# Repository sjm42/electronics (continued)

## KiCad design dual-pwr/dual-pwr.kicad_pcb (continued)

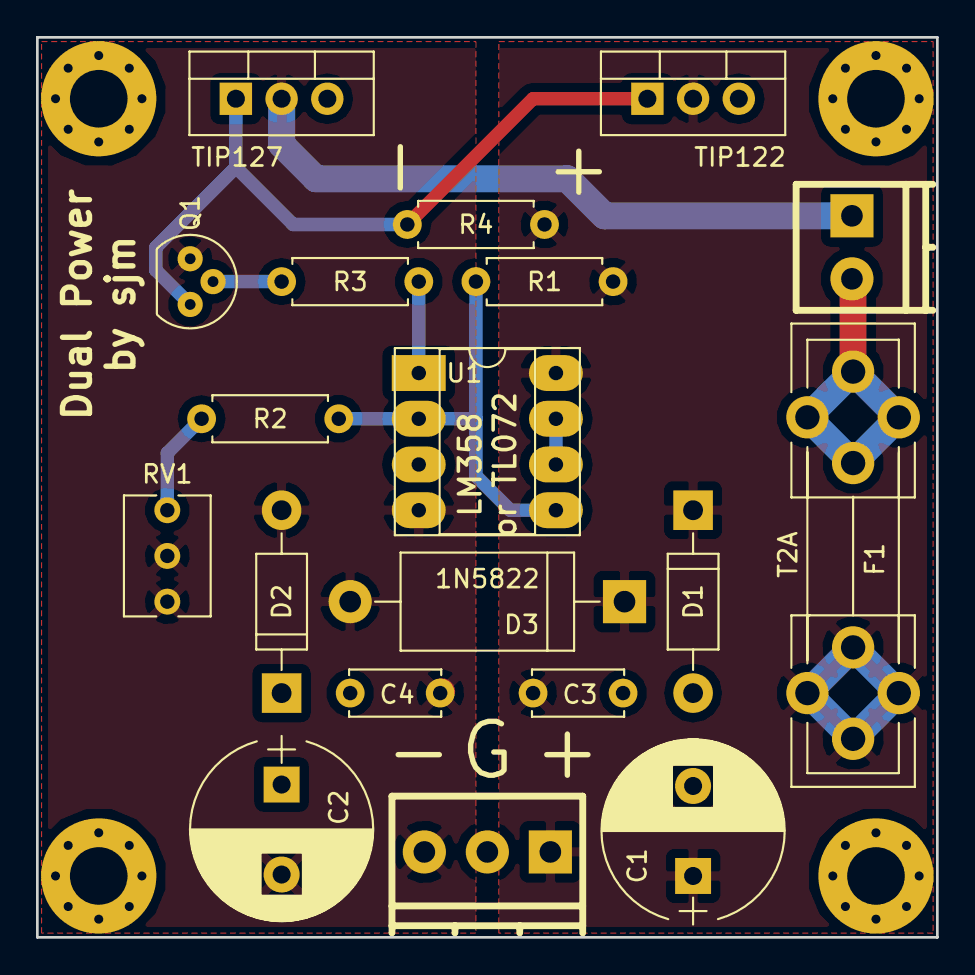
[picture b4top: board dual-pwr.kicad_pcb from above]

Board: 2 copper layers, 50.0 x 50.0 mm, 23 parts (0 on the bottom side), 10 nets.

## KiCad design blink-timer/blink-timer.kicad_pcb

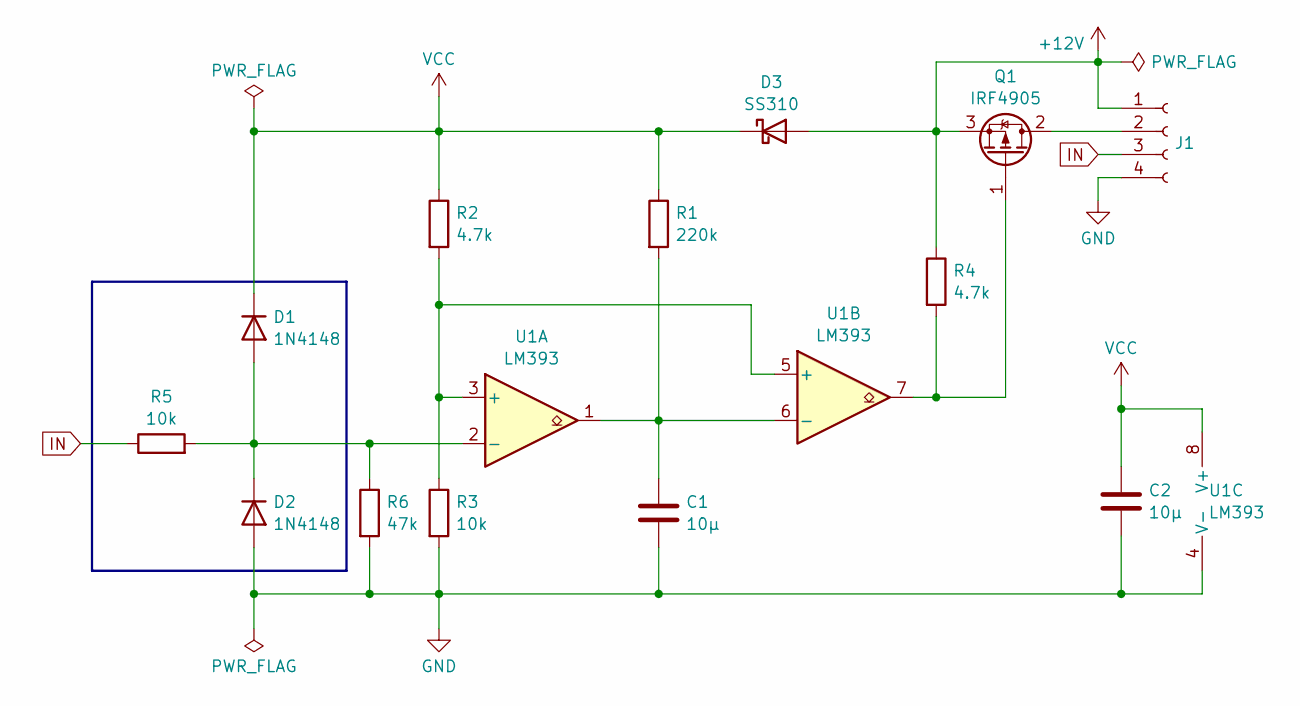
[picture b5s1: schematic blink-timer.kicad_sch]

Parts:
C1, C2: 10µ; C_1206_3216Metric_Pad1.33x1.80mm_HandSolder
D1, D2: 1N4148; D_MiniMELF
D3: SS310; D_SMA
J1: Conn_01x04_Socket; Altech_AK100_1x04_P5.00mm
Q1: IRF4905; TO-263-3_TabPin2
R1: 220k; R_0805_2012Metric_Pad1.20x1.40mm_HandSolder
R2, R4: 4.7k; R_0805_2012Metric_Pad1.20x1.40mm_HandSolder
R3, R5: 10k; R_0805_2012Metric_Pad1.20x1.40mm_HandSolder
R6: 47k; R_0805_2012Metric_Pad1.20x1.40mm_HandSolder
U1: LM393; SOIC-8_3.9x4.9mm_P1.27mm

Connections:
+12V: D3.2 (A), J1.1, Q1.3 (S), R4.1
GND: C1.2, C2.2, D2.2 (A), J1.4, R3.2, R6.2, U1.4 (V-)
IN: J1.3, R5.1
unnamed: D1.2 (A), D2.1 (K), R5.2, R6.1, U1.2 (-)
unnamed: J1.2, Q1.2 (D)
unnamed: Q1.1 (G), R4.2, U1.7
unnamed: R2.2, R3.1, U1.3 (+), U1.5 (+)
unnamed: C1.1, R1.2, U1.1, U1.6 (-)
VCC: C2.1, D1.1 (K), D3.1 (K), R1.1, R2.1, U1.8 (V+)

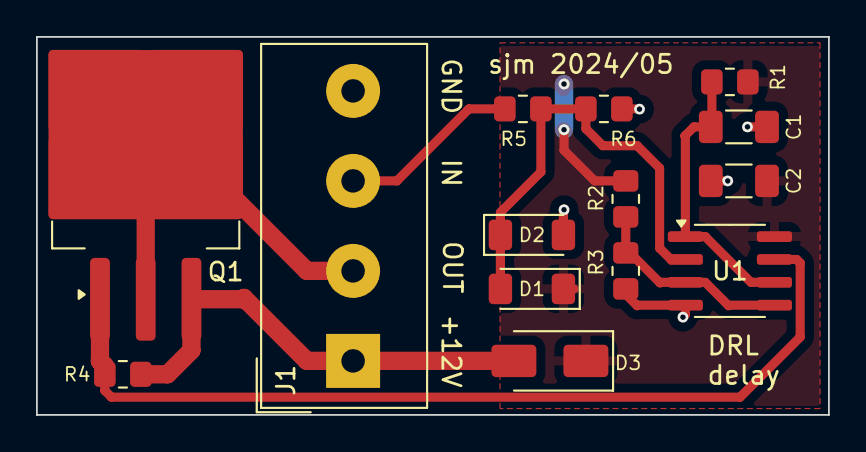
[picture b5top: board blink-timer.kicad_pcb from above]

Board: 2 copper layers, 44.0 x 21.0 mm, 14 parts (0 on the bottom side), 9 nets.

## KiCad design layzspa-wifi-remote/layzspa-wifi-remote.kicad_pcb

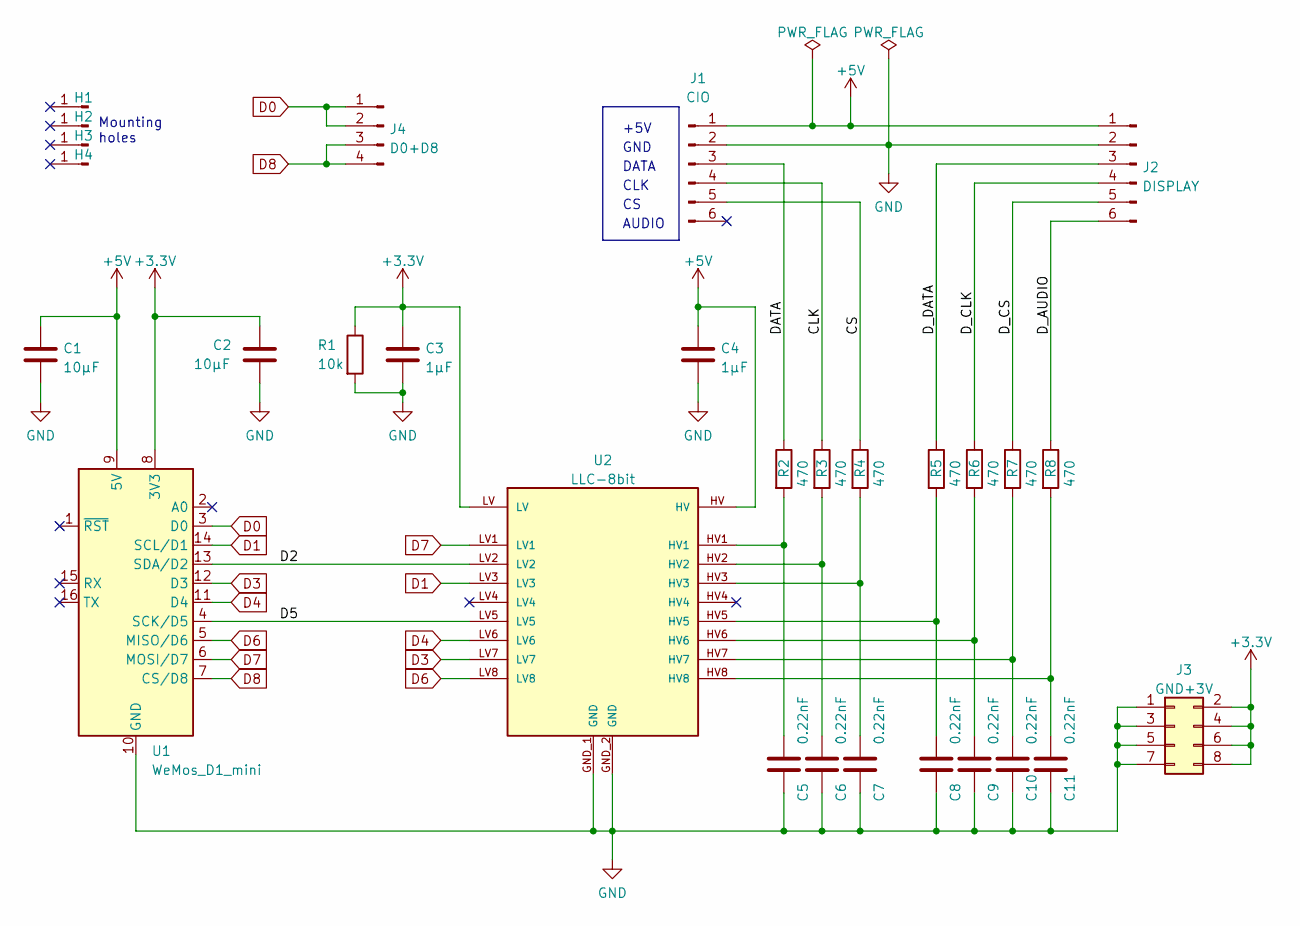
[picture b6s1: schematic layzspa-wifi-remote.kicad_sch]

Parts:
C1, C2: 10µF; C_Disc_D5.0mm_W2.5mm_P5.00mm
C3, C4: 1µF; C_Disc_D5.0mm_W2.5mm_P5.00mm
C5, C6, C7, C8, C9, C10, C11: 0.22nF; C_Disc_D5.0mm_W2.5mm_P5.00mm
H1, H2, H3, H4: Mounting hole; MountingHole_3.2mm_M3_ISO7380_Pad_TopBottom
J1: CIO; PinHeader_1x06_P2.54mm_Vertical
J2: DISPLAY; PinHeader_1x06_P2.54mm_Vertical
J3: GND+3V; PinHeader_2x04_P2.54mm_Vertical
J4: D0+D8; PinHeader_1x04_P2.54mm_Vertical
R1: 10k; R_1206_3216Metric_Pad1.30x1.75mm_HandSolder
R2, R3, R4, R5, R6, R7, R8: 470; R_1206_3216Metric_Pad1.30x1.75mm_HandSolder
U1: WeMos_D1_mini; WEMOS_D1_mini_light
U2: LLC-8bit; PARTREV 01

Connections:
+3.3V: C2.1, C3.1, J3.2, J3.4, J3.6, J3.8, R1.1, U1.8 (3V3), U2.LV
+5V: C1.1, C4.1, J1.1, J2.1, U1.9 (5V), U2.HV
/CLK: J1.4, R3.1
/CS: J1.5, R4.1
/D2: U1.13 (SDA/D2), U2.LV2
/D5: U1.4 (SCK/D5), U2.LV5
/DATA: J1.3, R2.1
/D_AUDIO: J2.6, R8.1
/D_CLK: J2.4, R6.1
/D_CS: J2.5, R7.1
/D_DATA: J2.3, R5.1
D0: J4.1, J4.2, U1.3 (D0)
D1: U1.14 (SCL/D1), U2.LV3
D3: U1.12 (D3), U2.LV7
D4: U1.11 (D4), U2.LV6
D6: U1.5 (MISO/D6), U2.LV8
D7: U1.6 (MOSI/D7), U2.LV1
D8: J4.3, J4.4, U1.7 (CS/D8)
GND: C1.2, C2.2, C3.2, C4.2, C5.2, C6.2, C7.2, C8.2, C9.2, C10.2, C11.2, J1.2, J2.2, J3.1, J3.3, J3.5, J3.7, R1.2, U1.10 (GND), U2.GND_1 (GND), U2.GND_2 (GND)
unnamed: C5.1, R2.2, U2.HV1
unnamed: C6.1, R3.2, U2.HV2
unnamed: C7.1, R4.2, U2.HV3
unnamed: C8.1, R5.2, U2.HV5
unnamed: C9.1, R6.2, U2.HV6
unnamed: C10.1, R7.2, U2.HV7
unnamed: C11.1, R8.2, U2.HV8

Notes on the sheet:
+5V
Mounting holes
AUDIO
DATA
GND
CLK

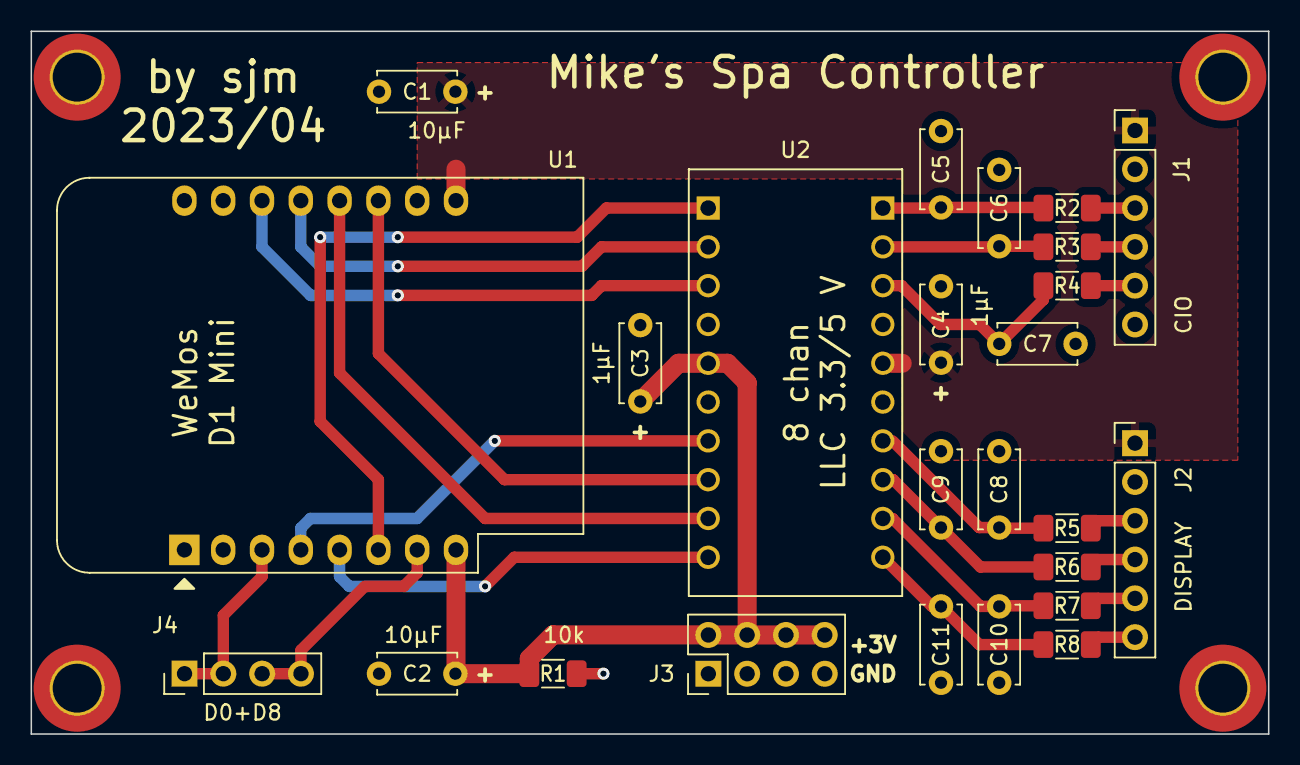
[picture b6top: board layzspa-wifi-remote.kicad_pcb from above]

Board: 2 copper layers, 81.0 x 46.0 mm, 29 parts (0 on the bottom side), 26 nets.

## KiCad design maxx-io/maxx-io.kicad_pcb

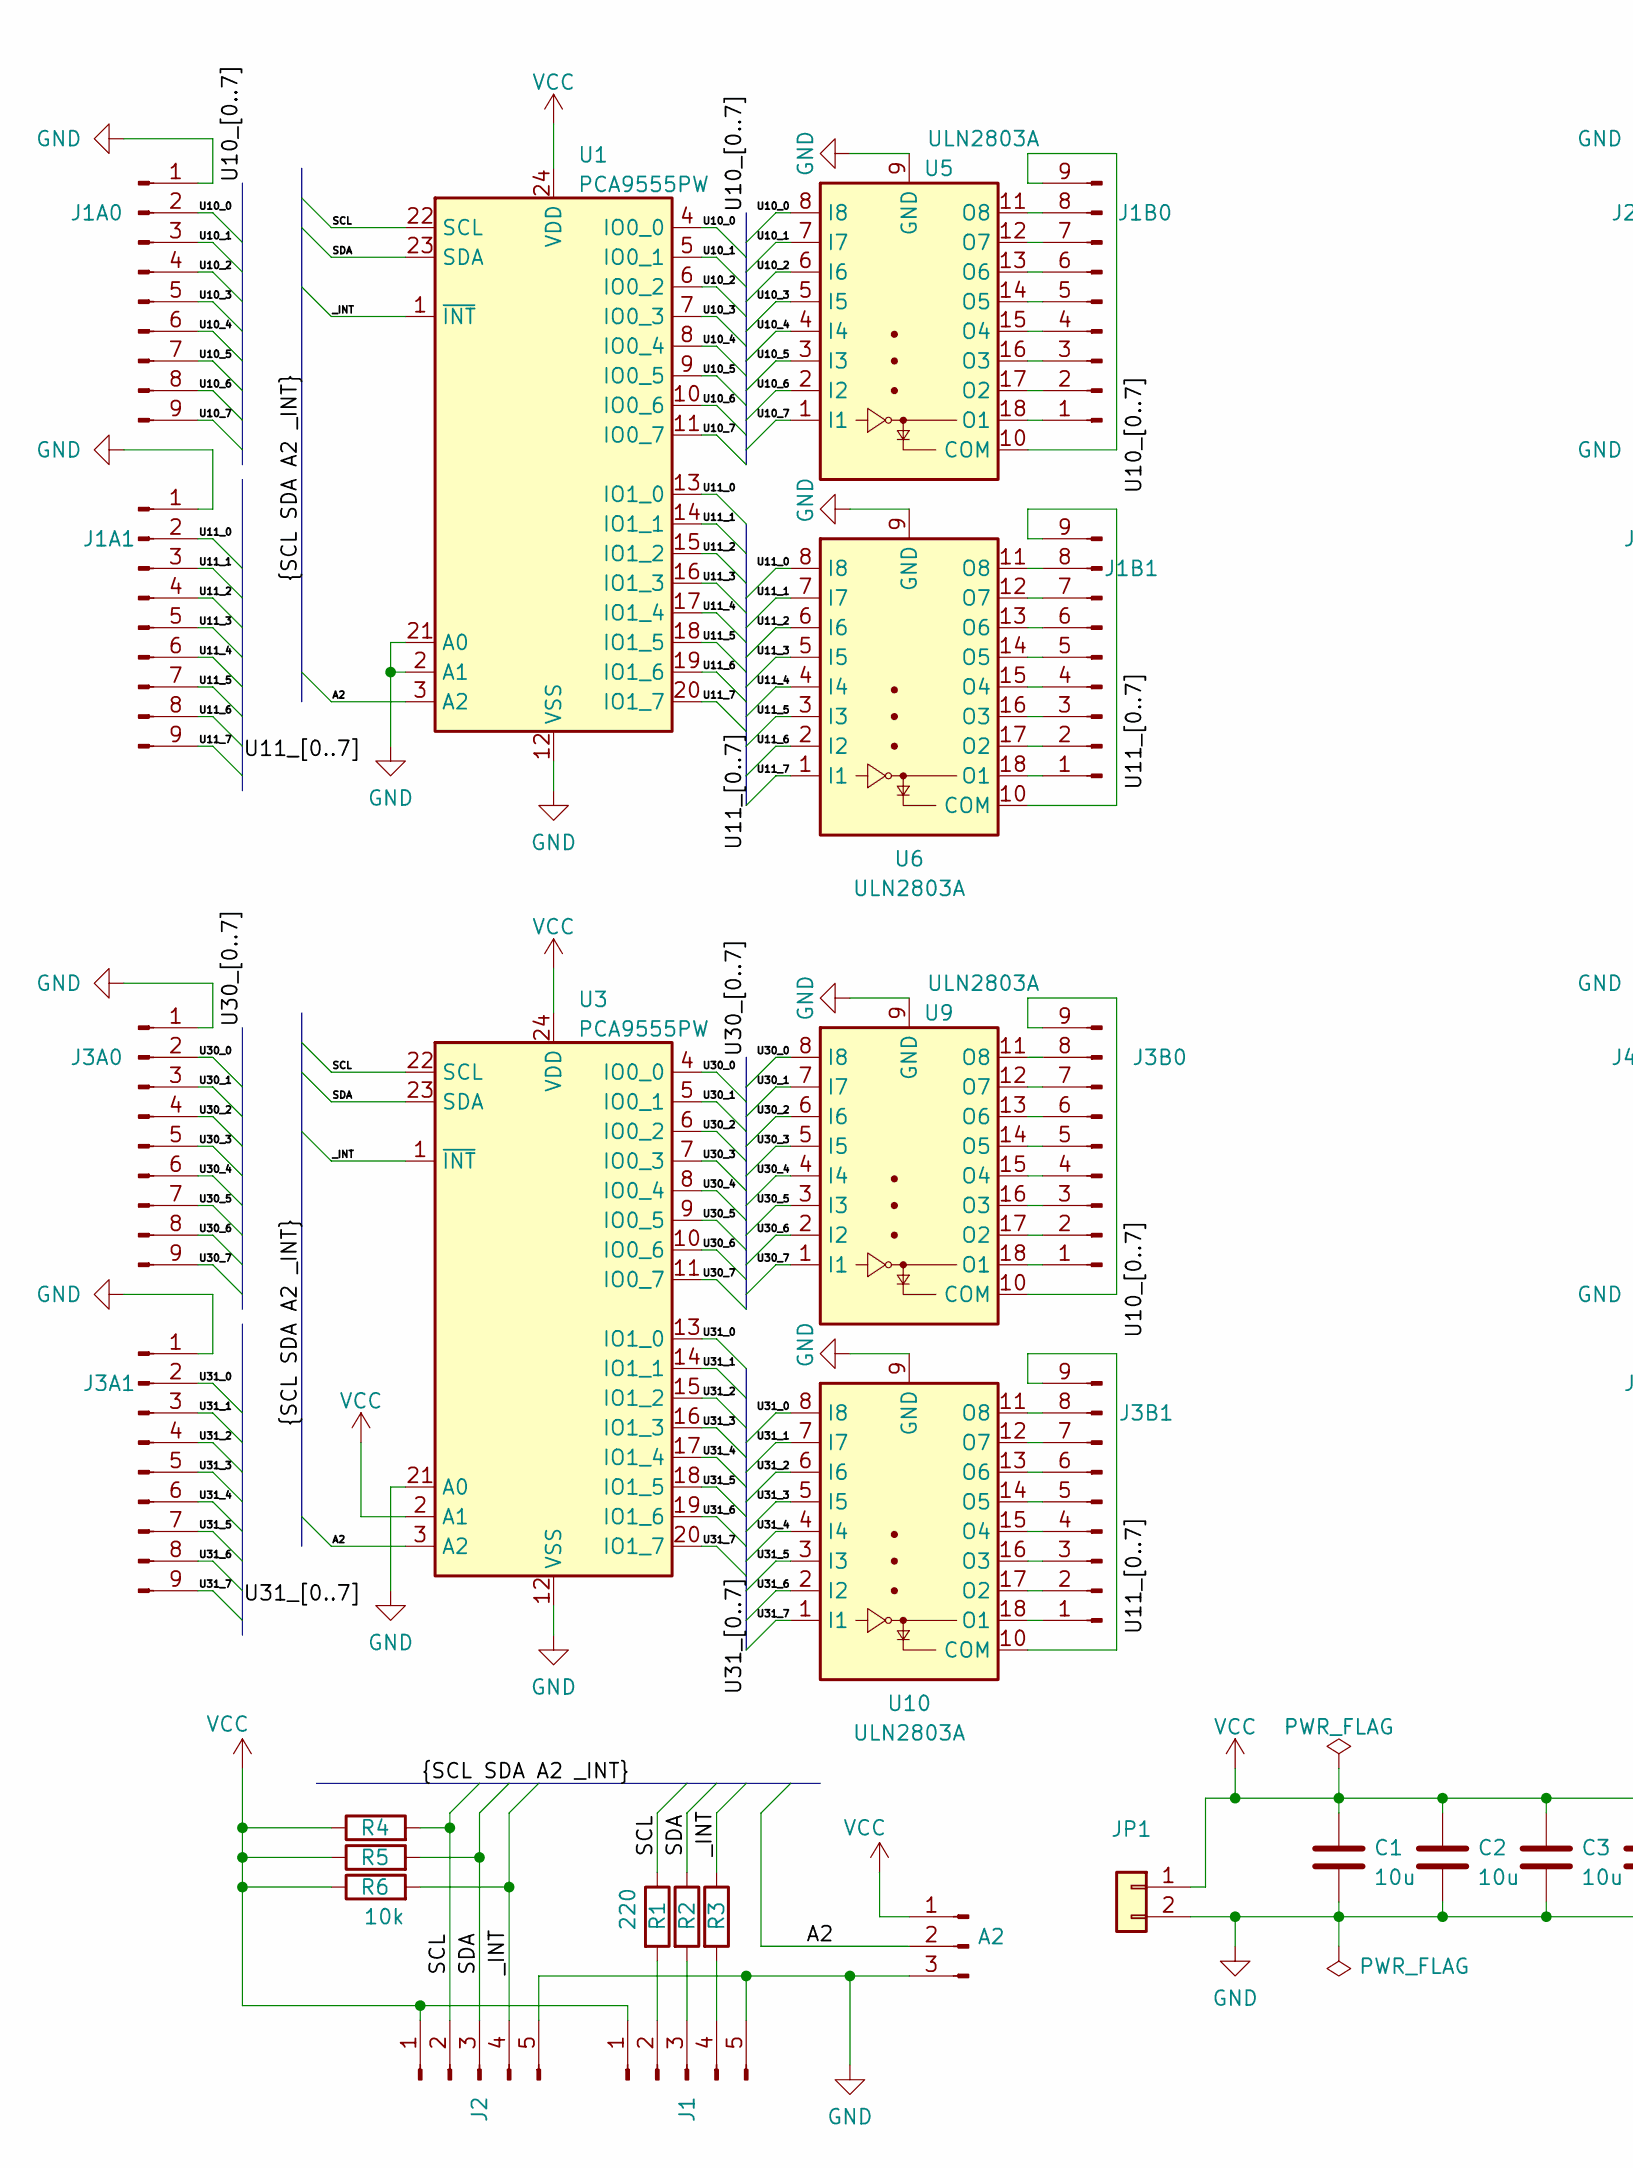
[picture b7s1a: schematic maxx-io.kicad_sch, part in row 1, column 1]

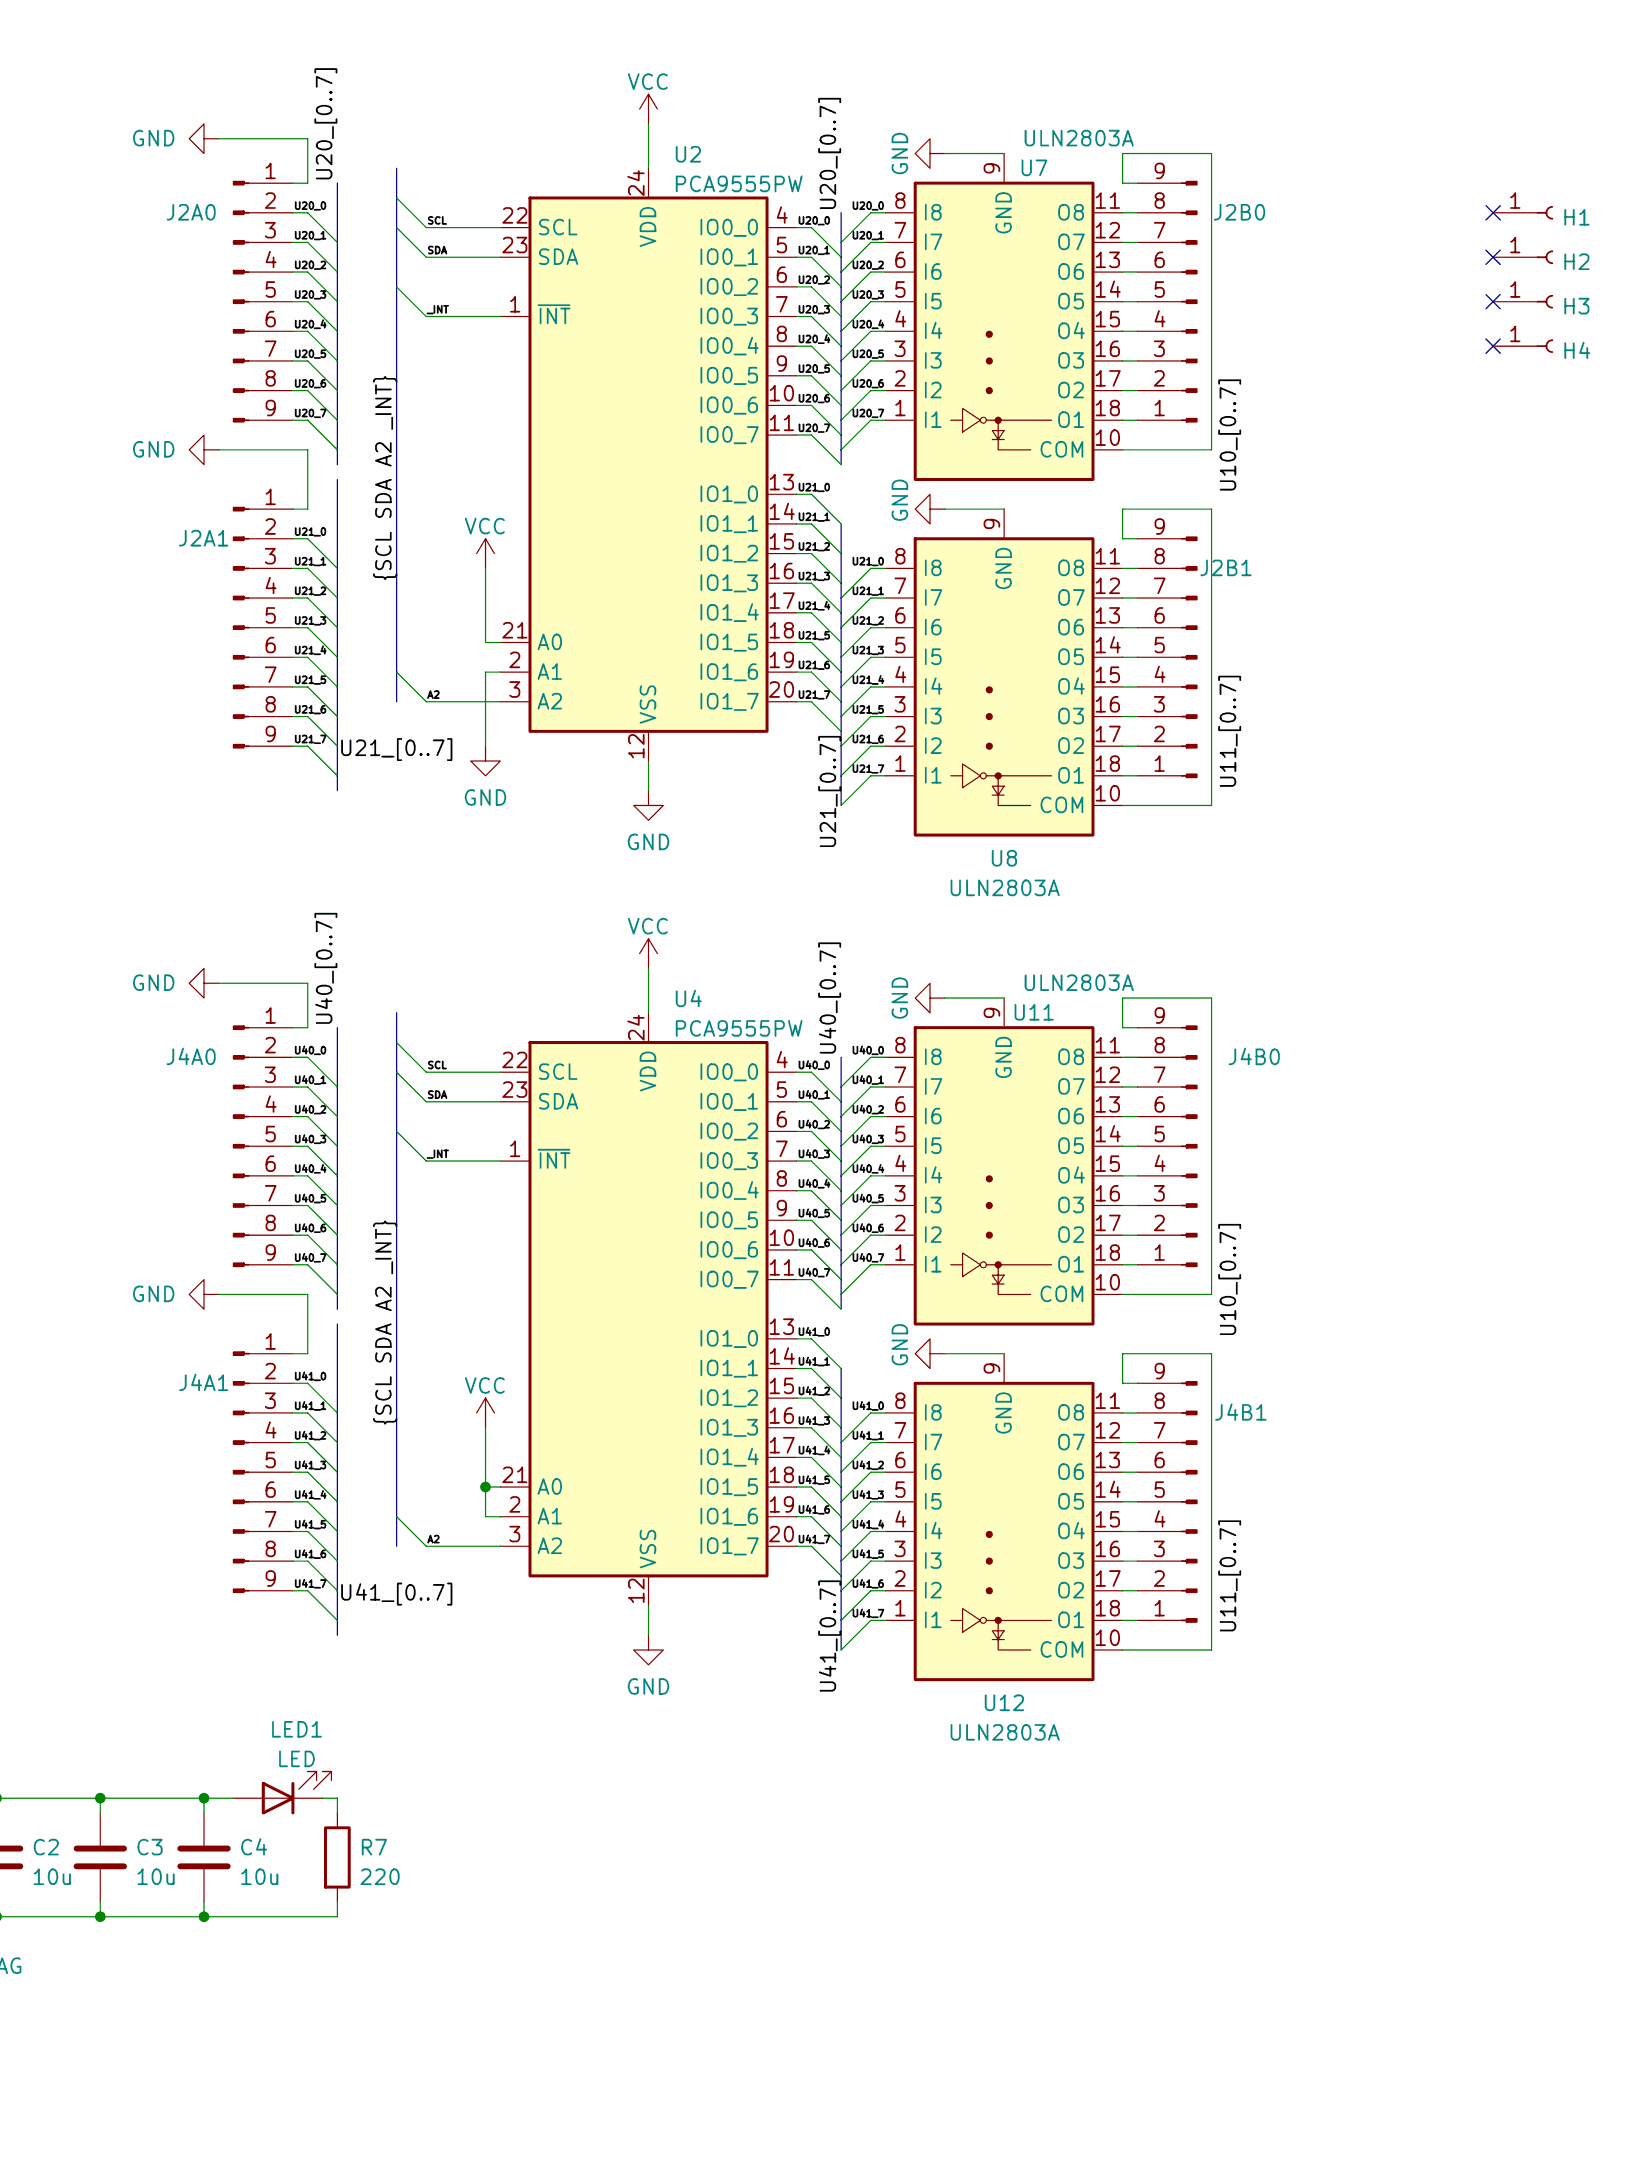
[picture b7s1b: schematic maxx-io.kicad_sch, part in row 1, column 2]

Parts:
A2: Conn_01x03_Male; PinHeader_1x03_P2.54mm_Vertical
C1, C2, C3, C4: 10u; C_Disc_D5.1mm_W3.2mm_P5.00mm
H1, H2, H3, H4: Conn_01x01_Female; MountingHole_3.2mm_M3_ISO14580_Pad
J1, J2: Conn_01x05_Male; PinHeader_1x05_P2.54mm_Vertical
J1A0, J1A1, J1B0, J1B1, J2A0, J2A1, J2B0, J2B1, J3A0, J3A1, J3B0, J3B1, J4A0, J4A1, J4B0, J4B1: Conn_01x09_Male; PinHeader_1x09_P2.54mm_Vertical
JP1: Conn_01x02; TerminalBlock_bornier-2_P5.08mm
LED1: LED; LED_1206_3216Metric_Pad1.42x1.75mm_HandSolder
R1, R2, R3, R7: 220; R_0805_2012Metric_Pad1.20x1.40mm_HandSolder
R4, R5, R6: 10k; R_0805_2012Metric_Pad1.20x1.40mm_HandSolder
U1, U2, U3, U4: PCA9555PW; TSSOP-24_4.4x7.8mm_P0.65mm
U5, U6, U7, U8, U9, U10, U11, U12: ULN2803A; SOP-18_7x12.5mm_P1.27mm

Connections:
/A2: A2.2, U1.3 (A2), U2.3 (A2), U3.3 (A2), U4.3 (A2)
/SCL: J2.2, R1.1, R4.2, U1.22 (SCL), U2.22 (SCL), U3.22 (SCL), U4.22 (SCL)
/SDA: J2.3, R2.1, R5.2, U1.23 (SDA), U2.23 (SDA), U3.23 (SDA), U4.23 (SDA)
/U10_0: J1A0.2, U1.4 (IO0_0), U5.8 (I8)
/U10_1: J1A0.3, U1.5 (IO0_1), U5.7 (I7)
/U10_2: J1A0.4, U1.6 (IO0_2), U5.6 (I6)
/U10_3: J1A0.5, U1.7 (IO0_3), U5.5 (I5)
/U10_4: J1A0.6, U1.8 (IO0_4), U5.4 (I4)
/U10_5: J1A0.7, U1.9 (IO0_5), U5.3 (I3)
/U10_6: J1A0.8, U1.10 (IO0_6), U5.2 (I2)
/U10_7: J1A0.9, U1.11 (IO0_7), U5.1 (I1)
/U11_0: J1A1.2, U1.13 (IO1_0), U6.8 (I8)
/U11_1: J1A1.3, U1.14 (IO1_1), U6.7 (I7)
/U11_2: J1A1.4, U1.15 (IO1_2), U6.6 (I6)
/U11_3: J1A1.5, U1.16 (IO1_3), U6.5 (I5)
/U11_4: J1A1.6, U1.17 (IO1_4), U6.4 (I4)
/U11_5: J1A1.7, U1.18 (IO1_5), U6.3 (I3)
/U11_6: J1A1.8, U1.19 (IO1_6), U6.2 (I2)
/U11_7: J1A1.9, U1.20 (IO1_7), U6.1 (I1)
/U20_0: J2A0.2, U2.4 (IO0_0), U7.8 (I8)
/U20_1: J2A0.3, U2.5 (IO0_1), U7.7 (I7)
/U20_2: J2A0.4, U2.6 (IO0_2), U7.6 (I6)
/U20_3: J2A0.5, U2.7 (IO0_3), U7.5 (I5)
/U20_4: J2A0.6, U2.8 (IO0_4), U7.4 (I4)
/U20_5: J2A0.7, U2.9 (IO0_5), U7.3 (I3)
/U20_6: J2A0.8, U2.10 (IO0_6), U7.2 (I2)
/U20_7: J2A0.9, U2.11 (IO0_7), U7.1 (I1)
/U21_0: J2A1.2, U2.13 (IO1_0), U8.8 (I8)
/U21_1: J2A1.3, U2.14 (IO1_1), U8.7 (I7)
/U21_2: J2A1.4, U2.15 (IO1_2), U8.6 (I6)
/U21_3: J2A1.5, U2.16 (IO1_3), U8.5 (I5)
/U21_4: J2A1.6, U2.17 (IO1_4), U8.4 (I4)
/U21_5: J2A1.7, U2.18 (IO1_5), U8.3 (I3)
/U21_6: J2A1.8, U2.19 (IO1_6), U8.2 (I2)
/U21_7: J2A1.9, U2.20 (IO1_7), U8.1 (I1)
/U30_0: J3A0.2, U3.4 (IO0_0), U9.8 (I8)
/U30_1: J3A0.3, U3.5 (IO0_1), U9.7 (I7)
/U30_2: J3A0.4, U3.6 (IO0_2), U9.6 (I6)
/U30_3: J3A0.5, U3.7 (IO0_3), U9.5 (I5)
/U30_4: J3A0.6, U3.8 (IO0_4), U9.4 (I4)
/U30_5: J3A0.7, U3.9 (IO0_5), U9.3 (I3)
/U30_6: J3A0.8, U3.10 (IO0_6), U9.2 (I2)
/U30_7: J3A0.9, U3.11 (IO0_7), U9.1 (I1)
/U31_0: J3A1.2, U3.13 (IO1_0), U10.8 (I8)
/U31_1: J3A1.3, U3.14 (IO1_1), U10.7 (I7)
/U31_2: J3A1.4, U3.15 (IO1_2), U10.6 (I6)
/U31_3: J3A1.5, U3.16 (IO1_3), U10.5 (I5)
/U31_4: J3A1.6, U3.17 (IO1_4), U10.4 (I4)
/U31_5: J3A1.7, U3.18 (IO1_5), U10.3 (I3)
/U31_6: J3A1.8, U3.19 (IO1_6), U10.2 (I2)
/U31_7: J3A1.9, U3.20 (IO1_7), U10.1 (I1)
/U40_0: J4A0.2, U4.4 (IO0_0), U11.8 (I8)
/U40_1: J4A0.3, U4.5 (IO0_1), U11.7 (I7)
/U40_2: J4A0.4, U4.6 (IO0_2), U11.6 (I6)
/U40_3: J4A0.5, U4.7 (IO0_3), U11.5 (I5)
/U40_4: J4A0.6, U4.8 (IO0_4), U11.4 (I4)
/U40_5: J4A0.7, U4.9 (IO0_5), U11.3 (I3)
/U40_6: J4A0.8, U4.10 (IO0_6), U11.2 (I2)
/U40_7: J4A0.9, U4.11 (IO0_7), U11.1 (I1)
/U41_0: J4A1.2, U4.13 (IO1_0), U12.8 (I8)
/U41_1: J4A1.3, U4.14 (IO1_1), U12.7 (I7)
/U41_2: J4A1.4, U4.15 (IO1_2), U12.6 (I6)
/U41_3: J4A1.5, U4.16 (IO1_3), U12.5 (I5)
/U41_4: J4A1.6, U4.17 (IO1_4), U12.4 (I4)
/U41_5: J4A1.7, U4.18 (IO1_5), U12.3 (I3)
/U41_6: J4A1.8, U4.19 (IO1_6), U12.2 (I2)
/U41_7: J4A1.9, U4.20 (IO1_7), U12.1 (I1)
/_INT: J2.4, R3.1, R6.2, U1.1 (~INT), U2.1 (~INT), U3.1 (~INT), U4.1 (~INT)
GND: A2.3, C1.2, C2.2, C3.2, C4.2, J1.5, J1A0.1, J1A1.1, J2.5, J2A0.1, J2A1.1, J3A0.1, J3A1.1, J4A0.1, J4A1.1, JP1.2, R7.2, U1.2 (A1), U1.12 (VSS), U1.21 (A0), U2.2 (A1), U2.12 (VSS), U3.12 (VSS), U3.21 (A0), U4.12 (VSS), U5.9 (GND), U6.9 (GND), U7.9 (GND), U8.9 (GND), U9.9 (GND), U10.9 (GND), U11.9 (GND), U12.9 (GND)
unnamed: J1.2, R1.2
unnamed: J1.3, R2.2
unnamed: J1.4, R3.2
unnamed: J1B0.1, U5.18 (O1)
unnamed: J1B0.2, U5.17 (O2)
unnamed: J1B0.3, U5.16 (O3)
unnamed: J1B0.4, U5.15 (O4)
unnamed: J1B0.5, U5.14 (O5)
unnamed: J1B0.6, U5.13 (O6)
unnamed: J1B0.7, U5.12 (O7)
unnamed: J1B0.8, U5.11 (O8)
unnamed: J1B0.9, U5.10 (COM)
unnamed: J1B1.1, U6.18 (O1)
unnamed: J1B1.2, U6.17 (O2)
unnamed: J1B1.3, U6.16 (O3)
unnamed: J1B1.4, U6.15 (O4)
unnamed: J1B1.5, U6.14 (O5)
unnamed: J1B1.6, U6.13 (O6)
unnamed: J1B1.7, U6.12 (O7)
unnamed: J1B1.8, U6.11 (O8)
unnamed: J1B1.9, U6.10 (COM)
unnamed: J2B0.1, U7.18 (O1)
unnamed: J2B0.2, U7.17 (O2)
unnamed: J2B0.3, U7.16 (O3)
unnamed: J2B0.4, U7.15 (O4)
unnamed: J2B0.5, U7.14 (O5)
unnamed: J2B0.6, U7.13 (O6)
unnamed: J2B0.7, U7.12 (O7)
unnamed: J2B0.8, U7.11 (O8)
unnamed: J2B0.9, U7.10 (COM)
unnamed: J2B1.1, U8.18 (O1)
unnamed: J2B1.2, U8.17 (O2)
unnamed: J2B1.3, U8.16 (O3)
unnamed: J2B1.4, U8.15 (O4)
unnamed: J2B1.5, U8.14 (O5)
unnamed: J2B1.6, U8.13 (O6)
unnamed: J2B1.7, U8.12 (O7)
unnamed: J2B1.8, U8.11 (O8)
unnamed: J2B1.9, U8.10 (COM)
unnamed: J3B0.1, U9.18 (O1)
unnamed: J3B0.2, U9.17 (O2)
unnamed: J3B0.3, U9.16 (O3)
unnamed: J3B0.4, U9.15 (O4)
unnamed: J3B0.5, U9.14 (O5)
unnamed: J3B0.6, U9.13 (O6)
unnamed: J3B0.7, U9.12 (O7)
unnamed: J3B0.8, U9.11 (O8)
unnamed: J3B0.9, U9.10 (COM)
unnamed: J3B1.1, U10.18 (O1)
unnamed: J3B1.2, U10.17 (O2)
unnamed: J3B1.3, U10.16 (O3)
unnamed: J3B1.4, U10.15 (O4)
unnamed: J3B1.5, U10.14 (O5)
unnamed: J3B1.6, U10.13 (O6)
unnamed: J3B1.7, U10.12 (O7)
unnamed: J3B1.8, U10.11 (O8)
unnamed: J3B1.9, U10.10 (COM)
unnamed: J4B0.1, U11.18 (O1)
unnamed: J4B0.2, U11.17 (O2)
unnamed: J4B0.3, U11.16 (O3)
unnamed: J4B0.4, U11.15 (O4)
unnamed: J4B0.5, U11.14 (O5)
unnamed: J4B0.6, U11.13 (O6)
unnamed: J4B0.7, U11.12 (O7)
unnamed: J4B0.8, U11.11 (O8)
unnamed: J4B0.9, U11.10 (COM)
unnamed: J4B1.1, U12.18 (O1)
unnamed: J4B1.2, U12.17 (O2)
unnamed: J4B1.3, U12.16 (O3)
unnamed: J4B1.4, U12.15 (O4)
unnamed: J4B1.5, U12.14 (O5)
unnamed: J4B1.6, U12.13 (O6)
unnamed: J4B1.7, U12.12 (O7)
unnamed: J4B1.8, U12.11 (O8)
unnamed: J4B1.9, U12.10 (COM)
unnamed: LED1.1 (K), R7.1
VCC: A2.1, C1.1, C2.1, C3.1, C4.1, J1.1, J2.1, JP1.1, LED1.2 (A), R4.1, R5.1, R6.1, U1.24 (VDD), U2.21 (A0), U2.24 (VDD), U3.2 (A1), U3.24 (VDD), U4.2 (A1), U4.21 (A0), U4.24 (VDD)

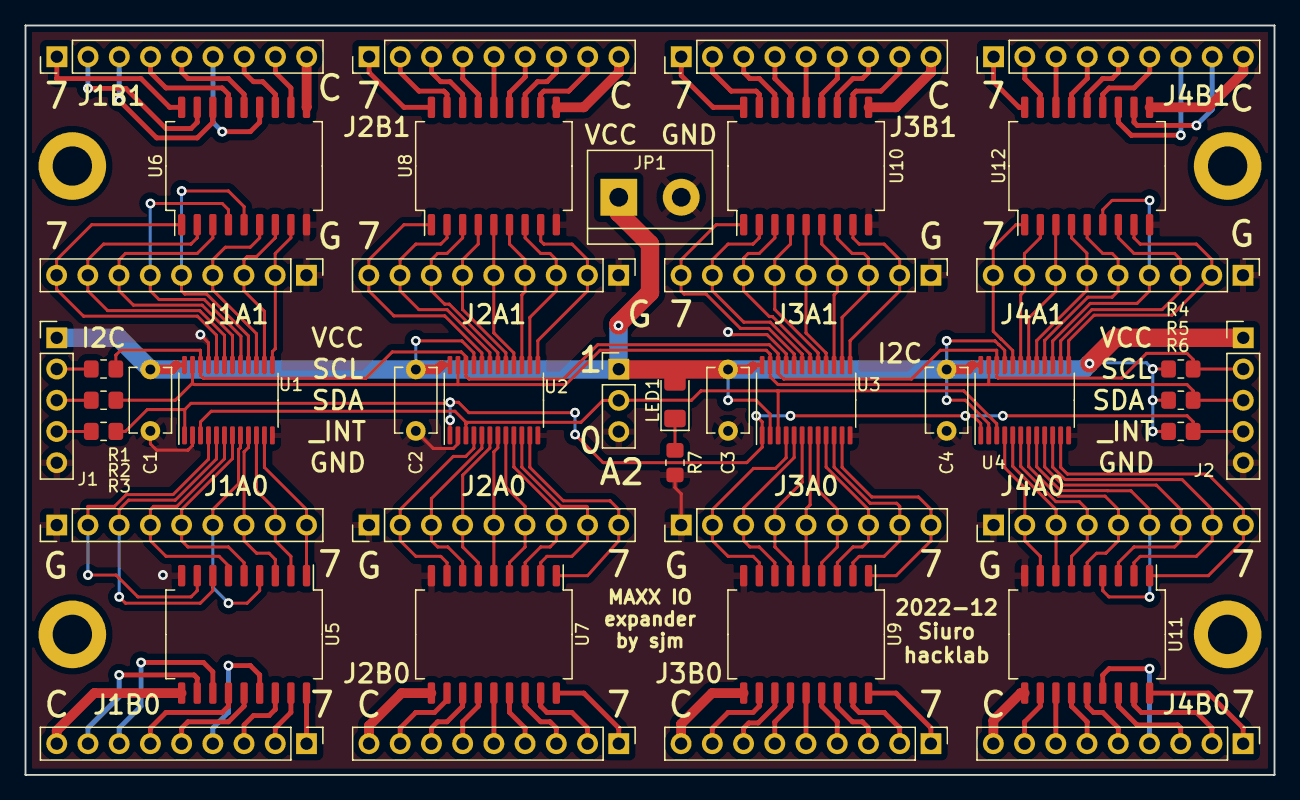
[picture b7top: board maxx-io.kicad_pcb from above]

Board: 2 copper layers, 101.6 x 61.0 mm, 48 parts (0 on the bottom side), 146 nets.

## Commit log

2018-03-13 dual-pwr
2023-01-28 Add maxx-io
2023-05-12 tunk
